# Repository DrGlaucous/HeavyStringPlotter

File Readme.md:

## String Plotter

---

  This is the repo for a whiteboard mounted string plotter, or *polarograph*.
It is designed to use standard 3D printer hardware and suction cups to mount to virtually any smooth surface or whiteboard. 
When not in use, it compacts nicely into a shoebox for easy transportation.

---
The plotter itself is not particularly fancy or innovative. Better designs probably exist.

What makes this plotter unique is that it makes use of the ESP32 and [FluidNC](https://github.com/bdring/FluidNC) for control. 

This allows versatile control over how the plotter will behave and a whole host of CAM software for generating plots, all wirelessly.

Several modifications have been made to the FluidNC firmware to optimize its use for this application.
New Commands:
* **$SAD = [distance in mm]** *Set Anchor Distance: set the distance between left and right anchor points when the plotter is set up.*
* **$DMC = [1/0]** *Direct Motor Control: Jogging with X and Y will move each motor directly without any kinematic conversion, to be used in conjunction with **\$CGL** *
* **$CGL = [0/1]** *Calibrate Gondola Location: 0 for left, 1 for right. Indented to help the plotter calculate the distance between anchors, but I find that using a tape measure and the **\$SAD** command is quicker and easier.*

The commands assume the plotter's 0,0 is directly below the left anchor. How far down can be set in the config file (the one I used can be found in the firmware folder with the fluidNC build itself).

---
Hardware:

* For the controller, I used a ESP32 Lolin32 Lite board. These can be picked up for extremely cheap online compared to other ESP32 models.
* I used two A4988 stepStick modules to control the steppers, which were just what I had on hand. Any type of motor will work, so long as it has somewhat decent torque and a NEMA17 form factor.
* A cheap 9g servo is used to actuate the marker.
* A buck-boost regulator supplies 3.3 volts to the controller and servo.
* I used a refitted 12V laptop power supply to give the contraption power, but it should be able to work on any voltage within the stepper controller and regulator's range. (higher voltages will mean more holding torque from the motors.)

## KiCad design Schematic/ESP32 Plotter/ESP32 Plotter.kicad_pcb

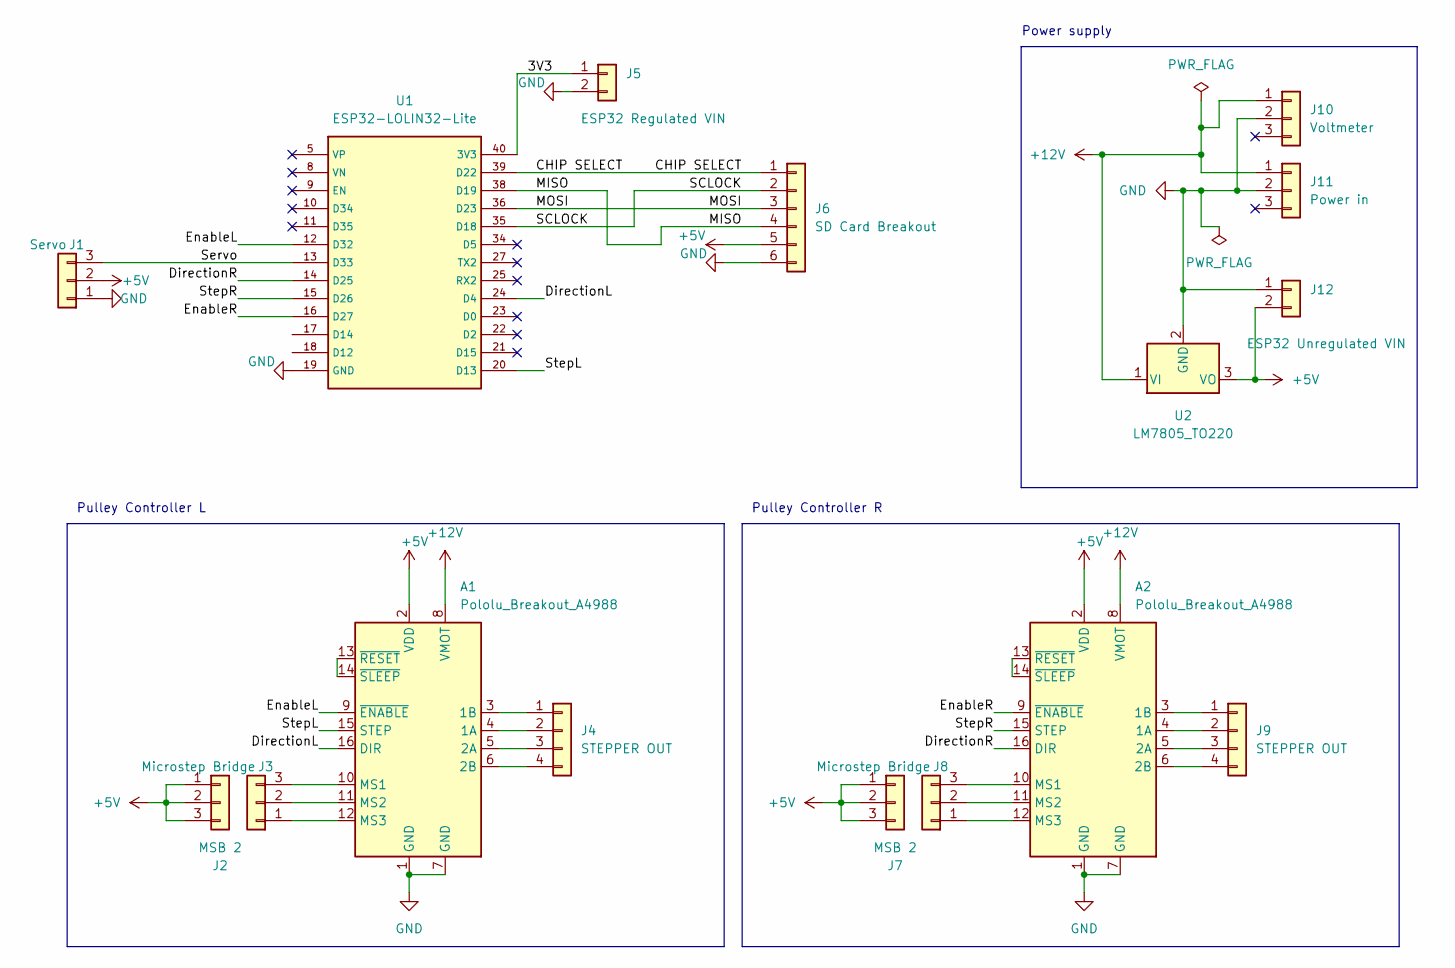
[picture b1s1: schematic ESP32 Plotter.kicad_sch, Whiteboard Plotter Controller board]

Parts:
A1, A2: Pololu_Breakout_A4988; Pololu_Breakout-16_15.2x20.3mm
J1: Servo; PinHeader_1x03_P2.54mm_Vertical
J2, J7: MSB 2; PinHeader_1x03_P2.54mm_Vertical
J3, J8: Microstep Bridge; PinHeader_1x03_P2.54mm_Vertical
J4, J9: STEPPER OUT; PinHeader_1x04_P2.54mm_Vertical
J5: ESP32 Regulated VIN; PinHeader_1x02_P2.54mm_Vertical
J6: SD Card Breakout; PinHeader_1x06_P2.54mm_Vertical
J10: Voltmeter; PinHeader_1x03_P2.54mm_Vertical
J11: Power in; PinHeader_1x03_P2.54mm_Vertical
J12: ESP32 Unregulated VIN; PinHeader_1x02_P2.54mm_Vertical
U1: ESP32-LOLIN32-Lite
U2: LM7805_TO220; TO-220-3_Vertical

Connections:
+5V: A1.2 (VDD), A2.2 (VDD), J1.2, J2.1, J2.2, J2.3, J6.5, J7.1, J7.2, J7.3, J12.2, U2.3 (VO)
+12V: A1.8 (VMOT), A2.8 (VMOT), J10.1, J11.1, U2.1 (VI)
/3V3: J5.1, U1.40 (3V3)
/CHIP SELECT: J6.1, U1.39 (D22)
/DirectionL: A1.16 (DIR), U1.24 (D4)
/DirectionR: A2.16 (DIR), U1.14 (D25)
/EnableL: A1.9 (~ENABLE), U1.12 (D32)
/EnableR: A2.9 (~ENABLE), U1.16 (D27)
/MISO: J6.4, U1.38 (D19)
/MOSI: J6.3, U1.36 (D23)
/SCLOCK: J6.2, U1.35 (D18)
/Servo: J1.3, U1.13 (D33)
/StepL: A1.15 (STEP), U1.20 (D13)
/StepR: A2.15 (STEP), U1.15 (D26)
GND: A1.1 (GND), A1.7 (GND), A2.1 (GND), A2.7 (GND), J1.1, J5.2, J6.6, J10.2, J11.2, J12.1, U1.19 (GND), U2.2 (GND)
unnamed: A1.3 (1B), J4.1
unnamed: A1.4 (1A), J4.2
unnamed: A1.5 (2A), J4.3
unnamed: A1.6 (2B), J4.4
unnamed: A1.10 (MS1), J3.3
unnamed: A1.11 (MS2), J3.2
unnamed: A1.12 (MS3), J3.1
unnamed: A1.13 (~RESET), A1.14 (~SLEEP)
unnamed: A2.3 (1B), J9.1
unnamed: A2.4 (1A), J9.2
unnamed: A2.5 (2A), J9.3
unnamed: A2.6 (2B), J9.4
unnamed: A2.10 (MS1), J8.3
unnamed: A2.11 (MS2), J8.2
unnamed: A2.12 (MS3), J8.1
unnamed: A2.13 (~RESET), A2.14 (~SLEEP)

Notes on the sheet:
Power supply
Pulley Controller R
Pulley Controller L

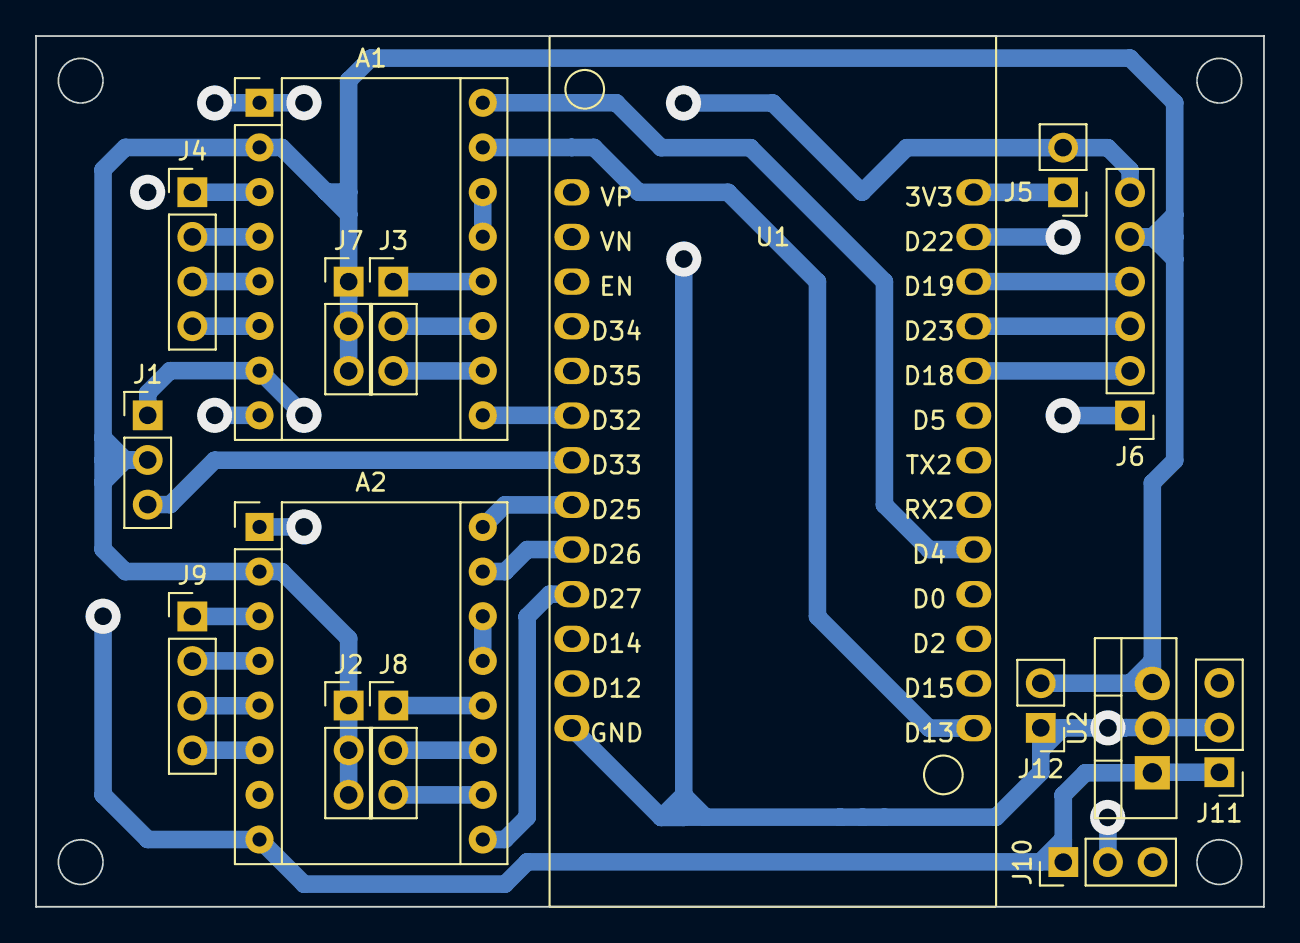
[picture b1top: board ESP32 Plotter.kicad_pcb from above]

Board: 2 copper layers, 69.8 x 49.5 mm, 16 parts (0 on the bottom side), 31 nets.

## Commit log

2023-02-20 Setup PCB and CNC milling paths
2023-02-22 Added programming references
    It's firmware time
2023-02-22 Switching to FluidNC
    has more and better CNC infrastructure, I just need to update a kinematics file (let's see if I can...)
2023-03-02 CAD trial and error
    I think I'm going to switch from a completely mobile unit to a stationary design (motors will be part of the anchor point rather than part of the gondola) because motors lack torque to lift the machi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
2023-03-16 STLs, Gcode, and many enhancements
2023-04-08 STLs and gcodes
    gcodes should probably be removed
2023-04-10 updates to fluidNC
    added $SAD and several other commands specific to kinematic settings, as well as removed a bug from the wallPlotter kinematics that caused undefined behavior.
2023-04-10 fixed bugs, added readme and images
2023-04-10 fix image link?
